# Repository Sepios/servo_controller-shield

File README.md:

servo_controller-shield
=======================

KiCad files (schemes, layouts, gerbers) for the Sepios servo controller shield, interconnecting the servo controller to the fin case cable.

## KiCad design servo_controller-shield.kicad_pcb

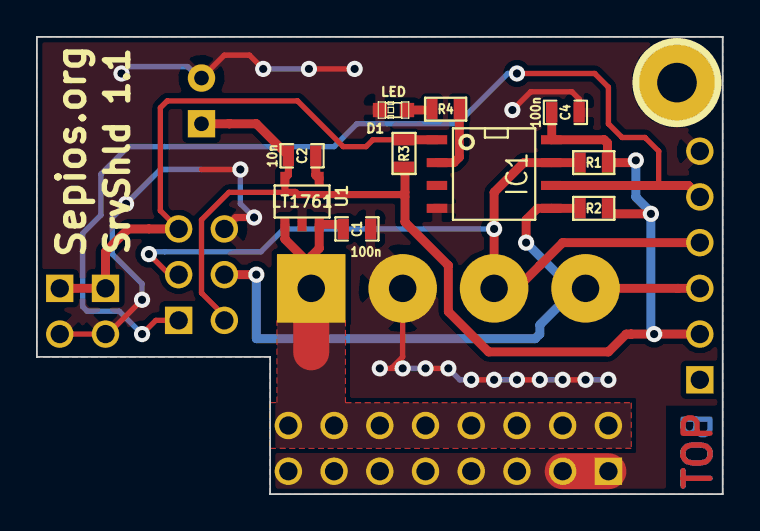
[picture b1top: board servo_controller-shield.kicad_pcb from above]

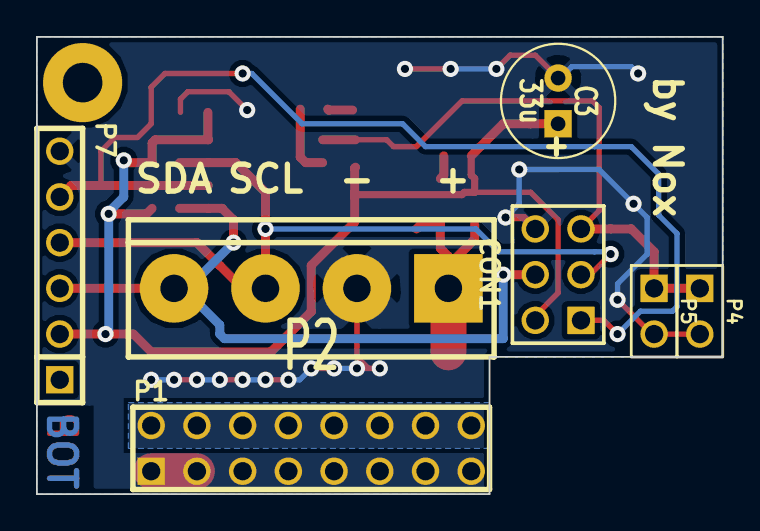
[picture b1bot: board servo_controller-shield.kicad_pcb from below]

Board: 2 copper layers, 38.1 x 25.4 mm, 18 parts (7 on the bottom side), 10 nets.

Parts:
1PIN: P***; 1pin
C1, C4: 100n; SM0603_Capa
C2: 10n; SM0603_Capa
C3: 33u; C1V7
CON1: AVR-ISP-6; pin_array_3x2
D1: LED; LED-0603
IC1: ATTINY85-S; SO8N
P1: SERVO_PWR; pin_array_8x2
P2: CONN_4; bornier4
P4: SENSOR0; PIN_ARRAY_2X1
P5: SENSOR1; PIN_ARRAY_2X1
P7: SERVO_IO; PIN_ARRAY-6X1
R1, R2: 4.7k; SM0603
R3: 47k; SM0603
R4: 680; SM0603
U1: LT1761; SOT23-5

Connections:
+BATT: C1.1, P1.2, P1.4, P1.6, P1.8, P1.10, P1.12, P1.14, P1.16, P2.1, U1.1, U1.3
/SCL: CON1.3, IC1.7, P2.3, P7.4, R1.2
/SDA: CON1.4, IC1.5, P2.4, P7.3, R2.2
GND: C1.2, C3.2, C4.2, CON1.6, D1.2, IC1.4, P1.1, P1.3, P1.5, P1.7, P1.9, P1.11, P1.13, P1.15, P2.2, P4.2, P5.2, P7.6, U1.2
unnamed: CON1.1, IC1.6, P7.5
unnamed: CON1.5, IC1.1, P4.1, P5.1, R3.1
unnamed: IC1.2, R4.1
unnamed: C2.2, U1.4
unnamed: D1.1, R4.2
VCC: C2.1, C3.1, C4.1, CON1.2, IC1.8, P7.2, R1.1, R2.1, R3.2, U1.5

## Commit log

2014-06-14 Add KiCad files
2014-06-14 Add PDF
